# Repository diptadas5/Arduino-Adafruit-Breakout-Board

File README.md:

# Arduino Ethernet Shield
* This board is created using Eagle CAD. The breakout board connects an Arduino Due A pin outs to a Adafruit Featherwing. 
* This allows the arduino to take advantage of the ethernet capabilities of the adafruit feather.
* The devices communicate through SPI, allowing TCP and UDP communications.

# Process of Manufacturing:
* First, we understand the requirements of the board. This board was a simple breakout board that only required the SPI connections and a few pinouts from the arduino to be connected to the feather. Therefore we first drew the schematic:

* After drawing the schematic, the floorplan of the board is next. This is where the floorplan was layed out on a physical board.

* We can also have a glimpse of the manufacturer's prototype of the board through Eagle's Manufacturer's Board option.

# Finished Product

* Once the schematics and floorplan were established, we download the gerber files and upload them to a manufacturer's website, where the boards are ordered. Below are some images of the finished product.

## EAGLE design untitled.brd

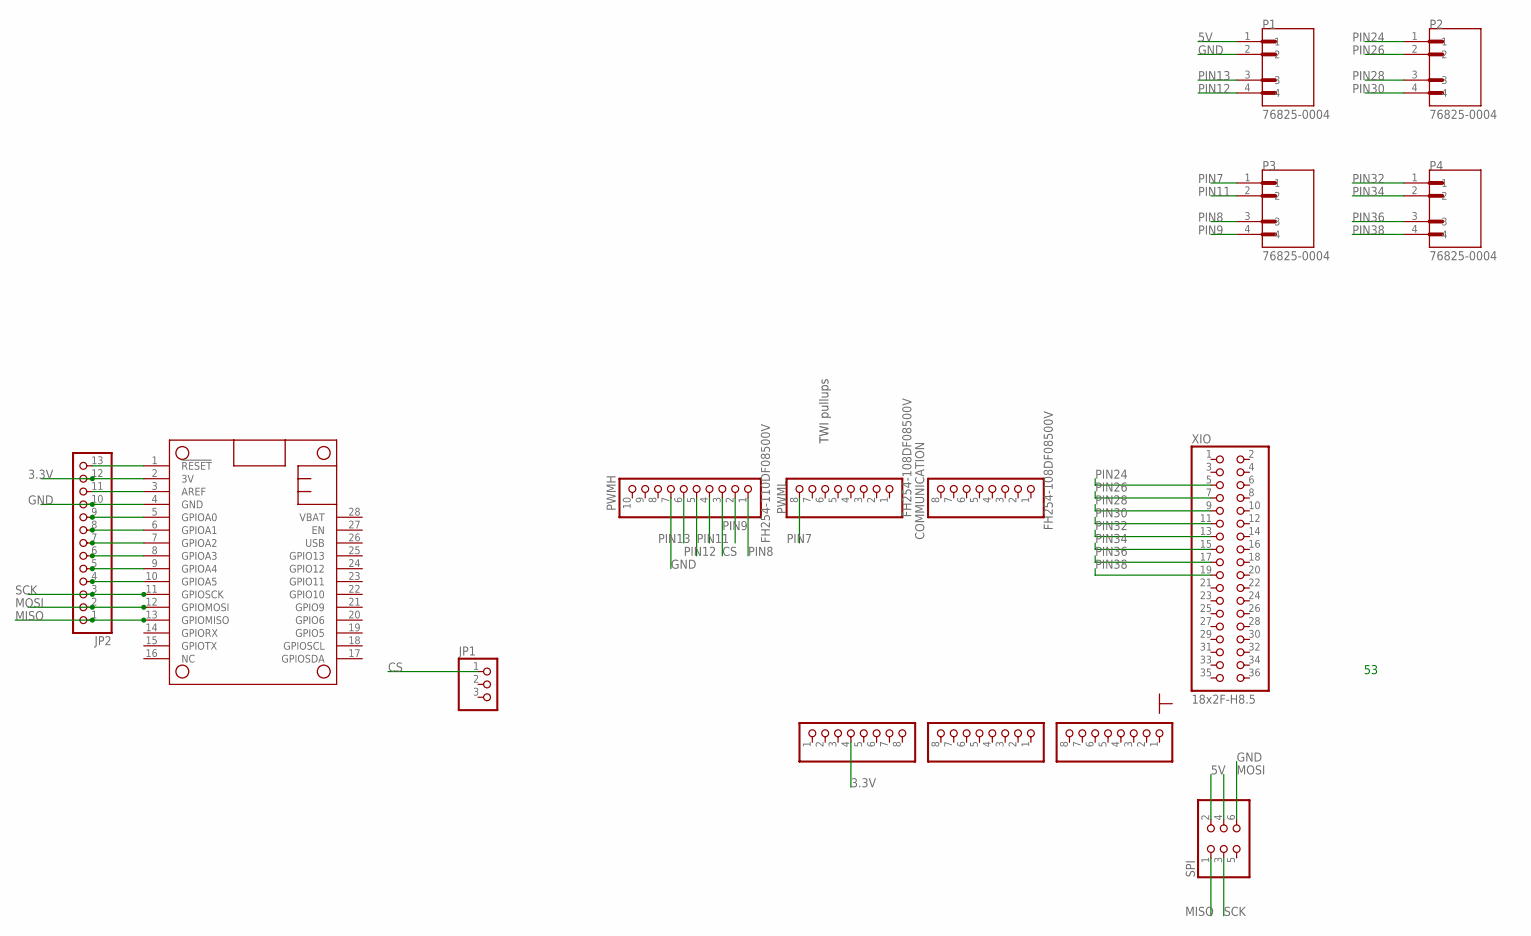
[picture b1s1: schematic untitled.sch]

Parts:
ADCH: FH254-108DF08500V; 1X08
ADCL: FH254-108DF08500V; 1X08
COMMUNICATION: FH254-108DF08500V; 1X08
JP1: HEADER-1X376MIL; 1X03_ROUND_76
JP2: HEADER-1X13; 1X13_ROUND_70
MS1: FEATHERWING_NODIM
P1, P2, P3, P4: 76825-0004; MOLEX_76825-0004
POWER: FH254-108DF08500V; 1X08
PWMH: FH254-110DF08500V; 1X10
PWML: FH254-108DF08500V; 1X08
SPI: ICSP; 2X03
XIO: 18x2F-H8.5; 2X18

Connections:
3.3V: JP2.11, JP2.12, MS1.2 (3V), MS1.3 (AREF), POWER.4
5V: P1.1, SPI.2
CS: JP1.1, PWMH.3
GND: JP2.10, MS1.4 (GND), P1.2, PWMH.7, SPI.6
MISO: JP2.1, MS1.13 (GPIOMISO), SPI.1
MOSI: JP2.2, MS1.12 (GPIOMOSI), SPI.4
unnamed: JP2.13, MS1.1 (!RESET)
unnamed: JP2.4, MS1.10 (GPIOA5)
unnamed: JP2.5, MS1.9 (GPIOA4)
unnamed: JP2.6, MS1.8 (GPIOA3)
unnamed: JP2.7, MS1.7 (GPIOA2)
unnamed: JP2.8, MS1.6 (GPIOA1)
unnamed: JP2.9, MS1.5 (GPIOA0)
PIN7: P3.1, PWML.8
PIN8: P3.3, PWMH.1
PIN9: P3.4, PWMH.2
PIN11: P3.2, PWMH.4
PIN12: P1.4, PWMH.5
PIN13: P1.3, PWMH.6
PIN24: P2.1, XIO.5
PIN26: P2.2, XIO.7
PIN28: P2.3, XIO.9
PIN30: P2.4, XIO.11
PIN32: P4.1, XIO.13
PIN34: P4.2, XIO.15
PIN36: P4.3, XIO.17
PIN38: P4.4, XIO.19
SCK: JP2.3, MS1.11 (GPIOSCK), SPI.3

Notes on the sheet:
TWI pullups

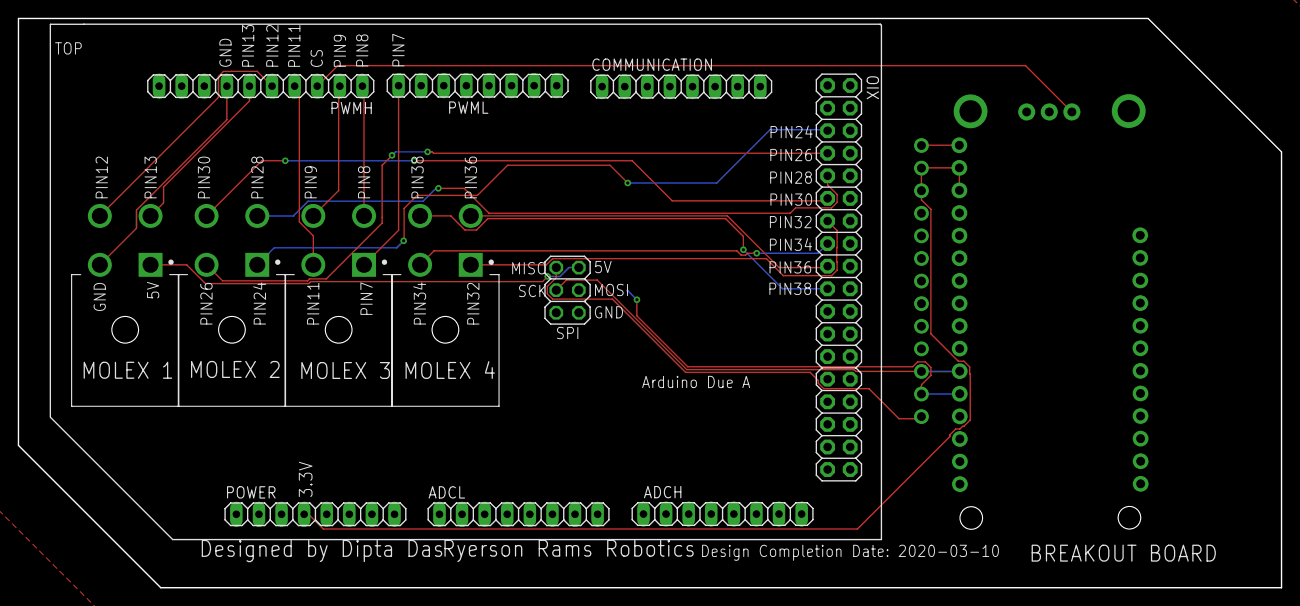
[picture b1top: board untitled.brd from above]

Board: 2 copper layers, 142.0 x 64.0 mm, 15 parts (0 on the bottom side), 28 nets.

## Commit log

2020-10-19 Breakout Board

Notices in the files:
parts and their libraries:
microbuilder: This work is placed in the public domain, and may be freely used for commercial and non-commercial work with the following conditions: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
